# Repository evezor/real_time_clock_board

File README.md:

# Real Time Clock Board
*please note this board has been deprecated.

This board has a real time clock module along with a battery backup. It will keep time over power cycles and also track days/months/years and time of day. 

source files can be found here: https://github.com/evezor/v0_real_time_clock_board

This board uses the Evezor Stamp STMF405 MCU

source: https://github.com/evezor/Evezor-Stamp-STMF405

Evezor® and all associated marks, logos, and designs are registered trademarks and protected by copyright. Unauthorized use or reproduction of these trademarks and copyrighted materials is strictly prohibited.

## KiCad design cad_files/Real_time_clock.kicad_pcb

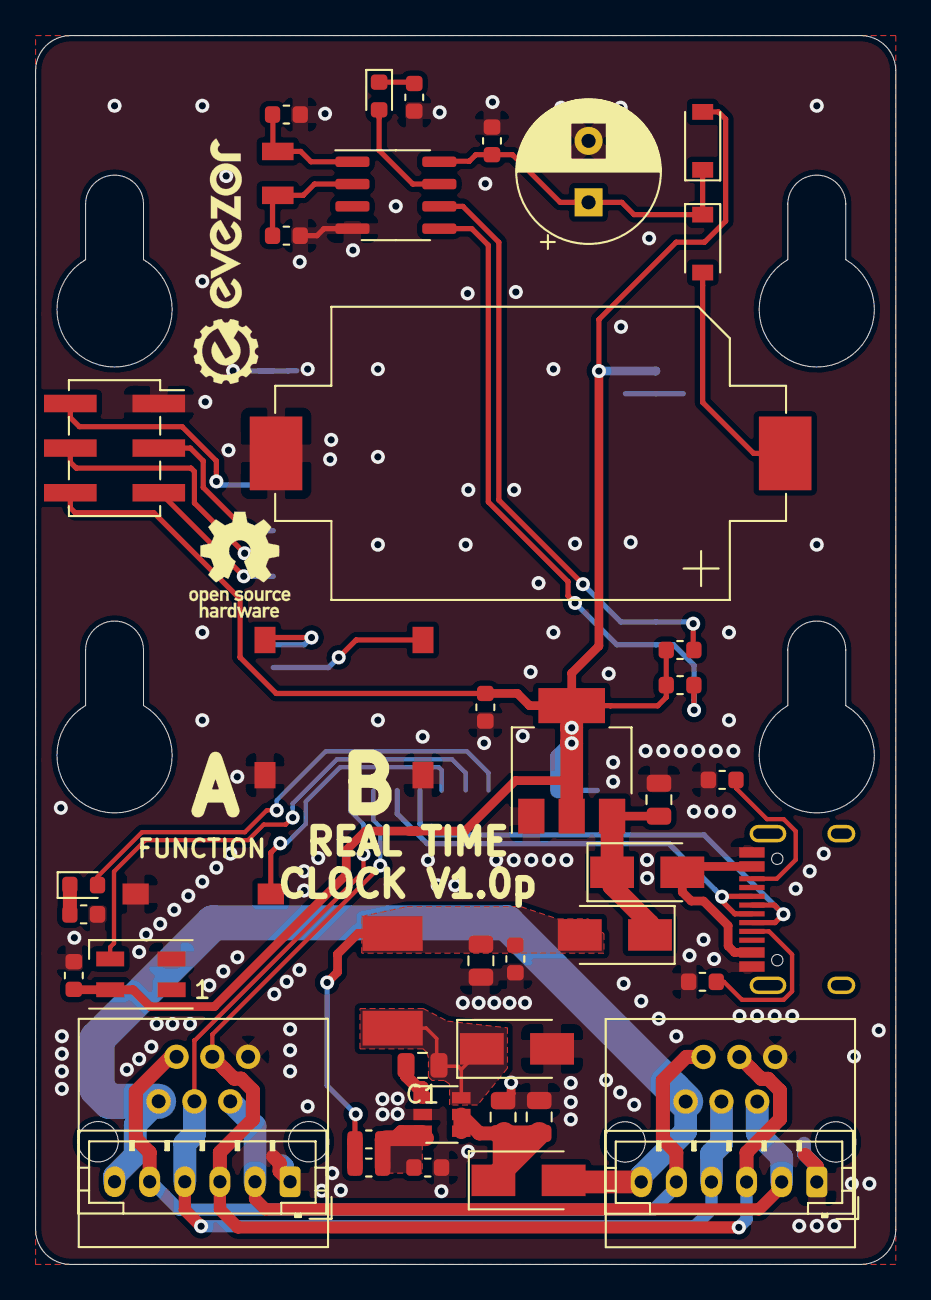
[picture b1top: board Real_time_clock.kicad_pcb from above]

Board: 2 copper layers, 49.0 x 70.0 mm, 46 parts (1 on the bottom side), 36 nets.

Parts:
BT1: Battery_Cell; BatteryHolder_Keystone_1060_1x2032
C1, C3: .1uF 100V; C_0805_2012Metric
C2, C5, C9, C10, C13: .1uF; C_0603_1608Metric
C4: 4.7uF; C_0805_2012Metric
C6: 22uF; C_0805_2012Metric
C7, C12: 12.5pF; C_0603_1608Metric
C8: 10uF; C_0805_2012Metric
C11: 1F; CP_Radial_D8.0mm_P3.50mm
D1, D2, D4, D5: SX35_SCHOTTKY; D_SMA
D3, D9: LED; LED_0603_1608Metric
D6: SK6812MINI; LED_SK6812MINI_PLCC4_3.5x3.5mm_P1.75mm
D7, D8: 1n4148; D_SOD-123
J1: USB_C_Receptacle_USB2.0; USB_C_Receptacle_HRO_TYPE-C-31-M-12
J2, J3: RJ11; RJ11_C189747_Horizontal
J4, J5: PH; JST_PH_B6B-PH-K_1x06_P2.00mm_Vertical
J6: Conn_02x03_Odd_Even; PinSocket_2x03_P2.54mm_Vertical_SMD
L1: 22uH; INDUCTOR_7.5X6.6_GCDA0630-220MC
R1: 10k; R_0603_1608Metric
R2: 82k; R_0603_1608Metric
R3, R4: 5.1k; R_0603_1608Metric
R5, R8: 15k; R_0603_1608Metric
R6, R7: 4.7k; R_0603_1608Metric
SW1, SW2, SW3: SW_Push; SWITCH_2x3_SMD_TACTILE_GREEN
U1: SY8401ABC; SOT-23-6
U2: AMS1117-3.3; SOT-223-3_TabPin2
U3: EDGE_STM32F405_CPU_V1; EDGE_STAMP
U4: RTC_REAL_TIME_CLOCK_PCF8563; SOIC-8_3.9x4.9mm_P1.27mm
Y1: Crystal; CRYSTAL_SEIKO_32.768_SC-32S32.768kHz20PPM12.5pF

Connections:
+3V3: C9.2, C10.1, D6.4, D8.2, J6.6, R6.1, R7.1, U2.2, U3.1, U3.18
/BOOT: J6.3, U3.36
/BUTTON_A: SW2.1, U3.31
/BUTTON_B: SW3.1, U3.30
/CAN_H: J2.3, J3.3, J4.3, J5.3, U3.26
/CAN_L: J2.4, J3.4, J4.4, J5.4, U3.27
/CC1: J1.A5, R4.1
/CC2: J1.B5, R3.1
/CLKOUT: D9.2, U4.7
/CLKPWR: C11.1, C13.2, D7.1, D8.1, U4.8
/D+: J1.A6, J1.B6, U3.25
/D-: J1.A7, J1.B7, U3.24
/FD_H: J2.2, J3.2, J4.2, J5.2
/FD_L: J2.5, J3.5, J4.5, J5.5
/FUNCTION_BUTTON: SW1.1, U3.23
/HBT_LED: D3.2, U3.21
/NEO_STATUS: D6.3, U3.22
/OLED_SCL: J6.5, U3.34
/OLED_SDA: J6.4, U3.35
/OSCI: C7.2, U4.1, Y1.2
/OSCO: C12.2, U4.2, Y1.1
/RESET: J6.2, U3.38
/SCL: R7.2, U3.12, U4.6
/SDA: R6.2, U3.13, U4.5
/USB_VCC: D4.2, J1.A4, J1.A9, J1.B4, J1.B9
/VREG_OUT: C2.1, C5.1, C6.1, D5.2, L1.2, R2.1
GND: BT1.2, C3.2, C4.2, C5.2, C6.2, C7.1, C8.2, C9.1, C10.2, C11.2, C12.1, C13.1, D1.2, D6.2, J1.A1, J1.A12, J1.B1, J1.B12, J2.1, J3.1, J4.1, J5.1, J6.1, R1.1, R3.2, R4.2, R5.1, R8.1, SW1.2, SW2.2, SW3.2, U1.2, U2.1, U3.2, U3.17, U3.43, U4.4
unnamed: BT1.1, D7.2
unnamed: C1.1, D1.1, L1.1, U1.6
unnamed: C1.2, U1.1
unnamed: C2.2, R1.2, R2.2, U1.3
unnamed: C3.1, C4.1, D2.1, U1.4, U1.5
unnamed: C8.1, D4.1, D5.1, U2.3
unnamed: D3.1, R5.2
unnamed: D9.1, R8.2
VBUS: D2.2, J2.6, J3.6, J4.6, J5.6

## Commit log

2020-12-18 ready for fab
2023-09-11 add pics
2023-09-11 Create LICENSE
